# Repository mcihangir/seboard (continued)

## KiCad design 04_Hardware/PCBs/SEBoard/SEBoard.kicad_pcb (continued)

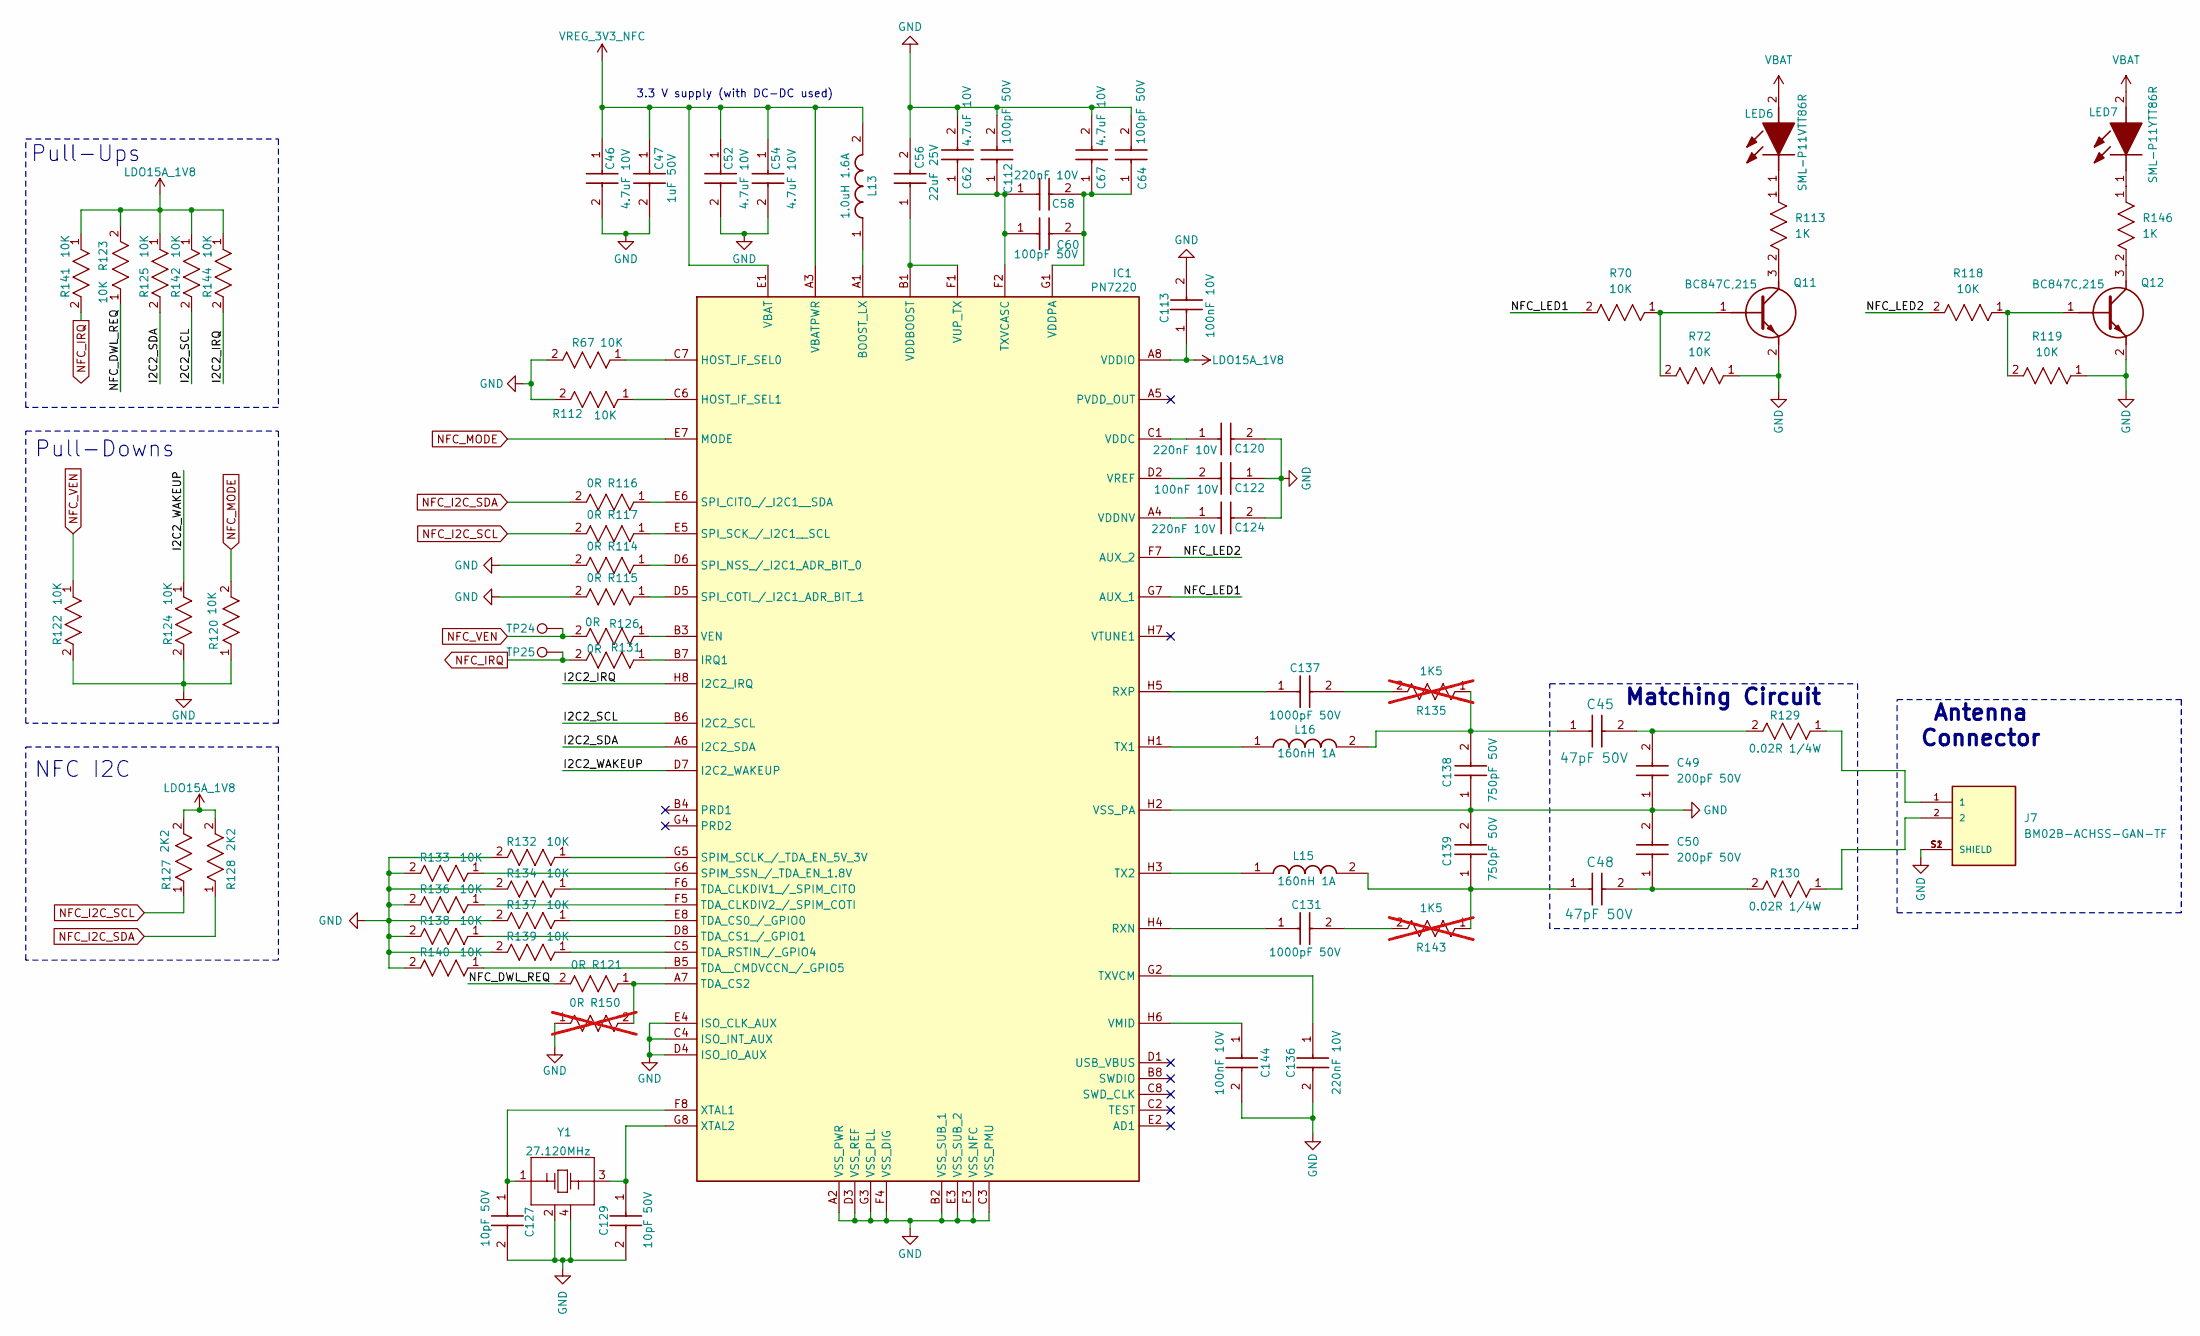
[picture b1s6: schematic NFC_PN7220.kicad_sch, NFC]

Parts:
C45, C48: 47pF 50V; CAP_CL10_SAM; Part Number 06035A470FAT2A
C46, C52, C54, C62, C67: 4.7uF 10V; CAPC1608X90N; Part Number LMK107BJ475KA-T
C47: 1uF 50V; CAPC1005X55N; Part Number GRM155R61H105KE05D
C49, C50: 200pF 50V; CAPC1608X87N; Part Number C0603C201F5GACTU
C56: 22uF 25V; CAPC2012X145N; Part Number GRM21BR61E226ME44L
C58, C120, C124, C136: 220nF 10V; CAPC1005X55N; Part Number GRM155R61A224JE19D
C60, C64, C112: 100pF 50V; CAPC1005X55N; Part Number GRM1555C1H101JA01J
C113, C122, C144: 100nF 10V; CAPC1005X55N; Part Number GRM155R71A104KA01D
C127, C129: 10pF 50V; CAPC1005X55N; Part Number GRM1555C1H100JA01D
C131, C137: 1000pF 50V; CAPC1608X80N; Part Number C1608C0G1H102F080AA
C138, C139: 750pF 50V; CAPC1608X87N; Part Number C0603C751F5GACTU
IC1: PN7220; BGA64C50P8X8_450X450X90; Part Number PN7220
J7: BM02B-ACHSS-GAN-TF; Part Number BM02B-ACHSS-GAN-TF(LF)(SN)
L13: 1.0uH 1.6A; LQM2HPN1R0MG0L; Part Number LQM2HPN1R0MG0L
L15, L16: 160nH 1A; LQW18CNR16J00D; Part Number LQW18CNR16J00D
LED6: SML-P11VTT86R; SMLP11VTT86R; Part Number SML-P11VTT86R
LED7: SML-P11YTT86R; SMLP11VTT86R; Part Number SML-P11YTT86R
Q11, Q12: BC847C,215; SOT95P230X110-3N; Part Number BC847C,215
R67, R70, R72, R112, R118, R119, R120, R122, R123, R124, R125, R132, R133, R134, R136, R137, R138, R139, R140, R141, R142, R144: 10K; RC0402N_YAG; Part Number RC0402JR-0710KL
R113, R146: 1K; RC0402N_YAG; Part Number RC0402JR-071KL
R114, R115, R116, R117, R121, R126, R131: 0R; RC0402N_YAG; Part Number RC0402JR-070RL
R127, R128: 2K2; RC0402N_YAG; Part Number RC0402JR-072K2L
R129, R130: 0.02R 1/4W; RESC2012X70N; Part Number RCWE080520L0FMEA
R135, R143: 1K5; ERJ3EKF1000V; Part Number ERJ-3GEYJ152V; not fitted
R150: 0R; RESC2012X50N; Part Number CRCW08050000Z0EA; not fitted
TP24, TP25: Sens_M; TestPoint_Pad_D1.0mm
Y1: 27.120MHz; ABM810000MHZ12D2W; Part Number ABM8-27.120MHZ-10-D1G-T

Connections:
/NFC_PN7220/I2C2_IRQ: IC1.H8 (I2C2_IRQ), R144.2
/NFC_PN7220/I2C2_SCL: IC1.B6 (I2C2_SCL), R142.2
/NFC_PN7220/I2C2_SDA: IC1.A6 (I2C2_SDA), R125.2
/NFC_PN7220/I2C2_WAKEUP: IC1.D7 (I2C2_WAKEUP), R124.1
/NFC_PN7220/NFC_DWL_REQ: R121.2, R123.1
/NFC_PN7220/NFC_LED1: IC1.G7 (AUX_1), R70.2
/NFC_PN7220/NFC_LED2: IC1.F7 (AUX_2), R118.2
GND: C46.2, C47.2, C49.1, C50.2, C52.2, C54.2, C56.2, C62.2, C64.2, C67.2, C112.2, C113.2, C120.2, C122.1, C124.2, C127.2, C129.2, C136.2, C138.1, C139.2, C144.2, IC1.A2 (VSS_PWR), IC1.B2 (VSS_SUB_1), IC1.C3 (VSS_PMU), IC1.C4 (ISO_INT_AUX), IC1.D3 (VSS_REF), IC1.D4 (ISO_IO_AUX), IC1.E3 (VSS_SUB_2), IC1.E4 (ISO_CLK_AUX), IC1.F3 (VSS_NFC), IC1.F4 (VSS_DIG), IC1.G3 (VSS_PLL), IC1.H2 (VSS_PA), J7.S1 (SHIELD), J7.S2 (SHIELD), Q11.2 (E), Q12.2 (E), R67.2, R72.1, R112.2, R114.2, R115.2, R119.1, R120.1, R122.2, R124.2, R132.2, R133.2, R134.2, R136.2, R137.2, R138.2, R139.2, R140.2, R150.1, Y1.2, Y1.4; also elsewhere on the board
LDO15A_1V8: C113.1, IC1.A8 (VDDIO), R123.2, R125.1, R127.2, R128.2, R141.1, R142.1, R144.1; also elsewhere on the board
NFC_I2C_SCL: R117.2, R127.1; also elsewhere on the board
NFC_I2C_SDA: R116.2, R128.1; also elsewhere on the board
NFC_IRQ: R131.2, R141.2, TP25.1 (1_1); also elsewhere on the board
NFC_MODE: IC1.E7 (MODE), R120.2; also elsewhere on the board
NFC_VEN: R122.1, R126.2, TP24.1 (1_1); also elsewhere on the board
unnamed: C45.2, C49.2, R129.2
unnamed: C48.2, C50.1, R130.2
unnamed: C131.2, R143.2
unnamed: C137.2, R135.2
unnamed: C45.1, C138.2, L16.2, R135.1
unnamed: C48.1, C139.1, L15.2, R143.1
unnamed: IC1.A1 (BOOST_LX), L13.1
unnamed: IC1.C7 (HOST_IF_SEL0), R67.1
unnamed: IC1.C6 (HOST_IF_SEL1), R112.1
unnamed: IC1.B7 (IRQ1), R131.1
unnamed: C131.1, IC1.H4 (RXN)
unnamed: C137.1, IC1.H5 (RXP)
unnamed: IC1.G5 (SPIM_SCLK_/_TDA_EN_5V_3V), R132.1
unnamed: IC1.G6 (SPIM_SSN_/_TDA_EN_1.8V), R133.1
unnamed: IC1.E6 (SPI_CITO_/_I2C1__SDA), R116.1
unnamed: IC1.D5 (SPI_COTI_/_I2C1_ADR_BIT_1), R115.1
unnamed: IC1.D6 (SPI_NSS_/_I2C1_ADR_BIT_0), R114.1
unnamed: IC1.E5 (SPI_SCK_/_I2C1__SCL), R117.1
unnamed: IC1.F6 (TDA_CLKDIV1_/_SPIM_CITO), R134.1
unnamed: IC1.F5 (TDA_CLKDIV2_/_SPIM_COTI), R136.1
unnamed: IC1.E8 (TDA_CS0_/_GPIO0), R137.1
unnamed: IC1.D8 (TDA_CS1_/_GPIO1), R138.1
unnamed: IC1.A7 (TDA_CS2), R121.1, R150.2
unnamed: IC1.C5 (TDA_RSTIN_/_GPIO4), R139.1
unnamed: IC1.B5 (TDA__CMDVCCN_/_GPIO5), R140.1
unnamed: IC1.H1 (TX1), L16.1
unnamed: IC1.H3 (TX2), L15.1
unnamed: C58.1, C60.1, C62.1, C112.1, IC1.F2 (TXVCASC)
unnamed: C136.1, IC1.G2 (TXVCM)
unnamed: C56.1, IC1.B1 (VDDBOOST), IC1.F1 (VUP_TX)
unnamed: C120.1, IC1.C1 (VDDC)
unnamed: C124.1, IC1.A4 (VDDNV)
unnamed: C58.2, C60.2, C64.1, C67.1, IC1.G1 (VDDPA)
unnamed: IC1.B3 (VEN), R126.1
unnamed: C144.1, IC1.H6 (VMID)
unnamed: C122.2, IC1.D2 (VREF)
unnamed: C127.1, IC1.F8 (XTAL1), Y1.1
unnamed: C129.1, IC1.G8 (XTAL2), Y1.3
unnamed: J7.1, R129.1
unnamed: J7.2, R130.1
unnamed: LED6.1 (K), R113.1
unnamed: LED7.1 (K), R146.1
unnamed: Q11.1 (B), R70.1, R72.2
unnamed: Q11.3 (C), R113.2
unnamed: Q12.1 (B), R118.1, R119.2
unnamed: Q12.3 (C), R146.2
VBAT: LED6.2 (A), LED7.2 (A); also elsewhere on the board
VREG_3V3_NFC: C46.1, C47.1, C52.1, C54.1, IC1.A3 (VBATPWR), IC1.E1 (VBAT), L13.2; also elsewhere on the board

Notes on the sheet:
NFC I2C
Pull-Ups
Antenna Connector
3.3 V supply (with DC-DC used)
Matching Circuit
Pull-Downs

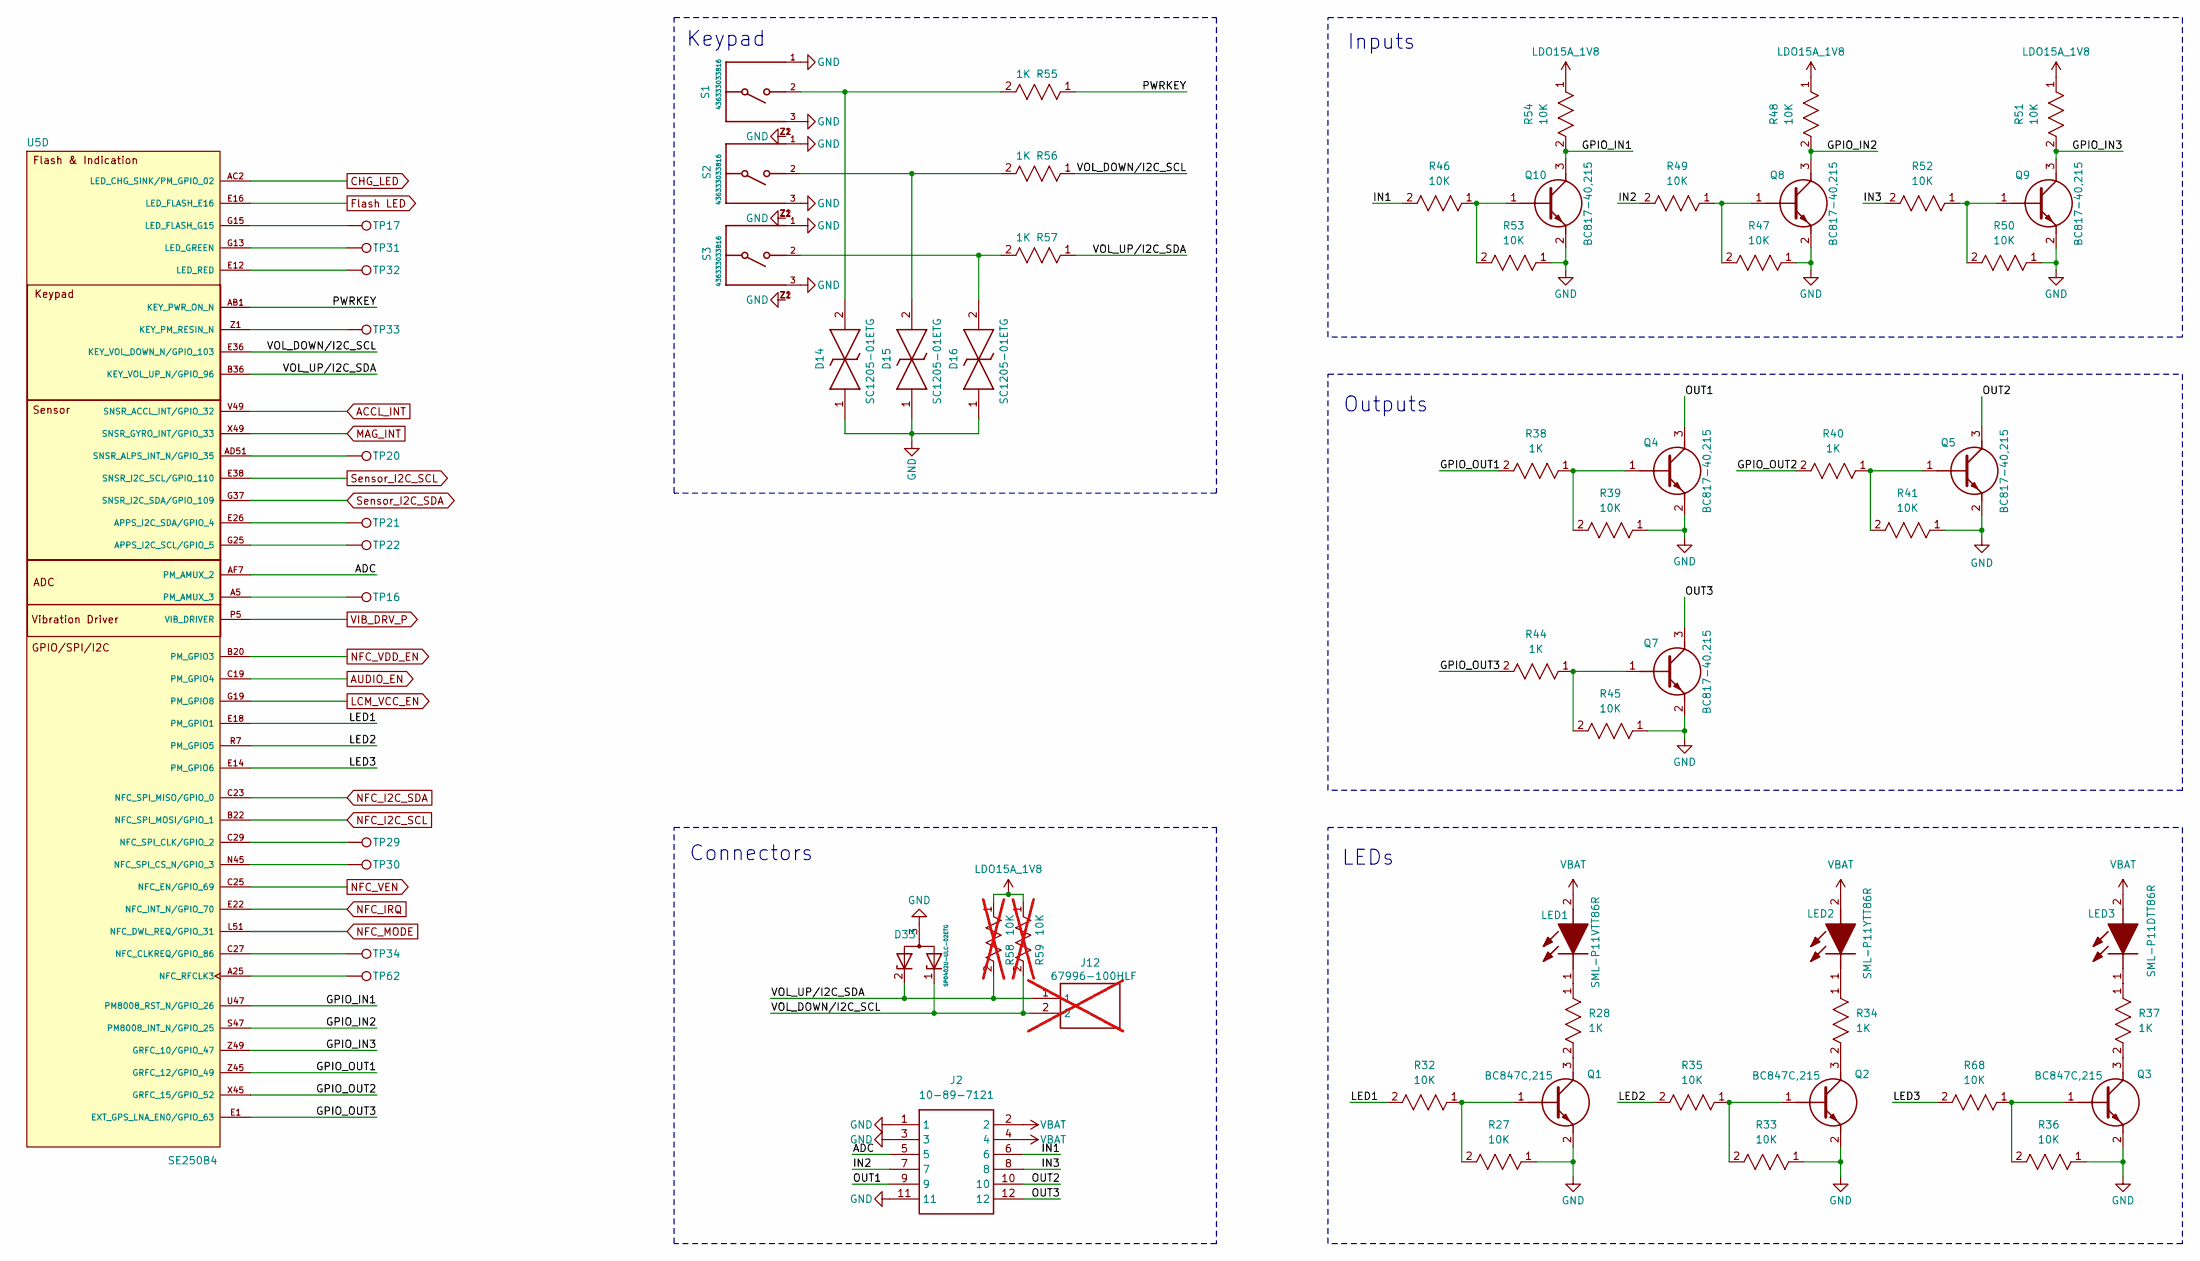
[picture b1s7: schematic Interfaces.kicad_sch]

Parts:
D14, D15, D16: SC1205-01ETG; SC120501ETG; Part Number SC1205-01ETG
D33: SP0402U-ULC-02ETG; SESD0402Q2UG0020090; Part Number SP0402U-ULC-02ETG
J2: 10-89-7121; HDRV12W87P254X254_2X6; Part Number 10-89-7121
J12: 67996-100HLF; HDRV2W67P254_2X1_254X483X858P; Part Number 67996-100HLF; not fitted
LED1: SML-P11VTT86R; SMLP11VTT86R; Part Number SML-P11VTT86R
LED2: SML-P11YTT86R; SMLP11VTT86R; Part Number SML-P11YTT86R
LED3: SML-P11DTT86R; SMLP11VTT86R; Part Number SML-P11DTT86R
Q1, Q2, Q3: BC847C,215; SOT95P230X110-3N; Part Number BC847C,215
Q4, Q5, Q7, Q8, Q9, Q10: BC817-40,215; BC81740215; Part Number BC817-40,215
R27, R32, R33, R35, R36, R39, R41, R45, R46, R47, R48, R49, R50, R51, R52, R53, R54, R68: 10K; RC0402N_YAG; Part Number RC0402JR-0710KL
R28, R34, R37, R38, R40, R44, R55, R56, R57: 1K; RC0402N_YAG; Part Number RC0402JR-071KL
R58, R59: 10K; RC0402N_YAG; Part Number RC0402JR-0710KL; not fitted
S1, S2, S3: 436333033816; Part Number 436333033816
TP16, TP17, TP20, TP21, TP22, TP29, TP30, TP31, TP32, TP33, TP34, TP62: Sens_M; TestPoint_Pad_D1.0mm
U5: SE250B4; XCVR_SE250B4-NA; Part Number SE250B4-EU

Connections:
/Interfaces/ADC: J2.5, U5.AF7 (PM_AMUX_2)
/Interfaces/GPIO_IN1: Q10.3 (C), R54.2, U5.U47 (PM8008_RST_N/GPIO_26)
/Interfaces/GPIO_IN2: Q8.3 (C), R48.2, U5.S47 (PM8008_INT_N/GPIO_25)
/Interfaces/GPIO_IN3: Q9.3 (C), R51.2, U5.Z49 (GRFC_10/GPIO_47)
/Interfaces/GPIO_OUT1: R38.2, U5.Z45 (GRFC_12/GPIO_49)
/Interfaces/GPIO_OUT2: R40.2, U5.X45 (GRFC_15/GPIO_52)
/Interfaces/GPIO_OUT3: R44.2, U5.E1 (EXT_GPS_LNA_EN0/GPIO_63)
/Interfaces/IN1: J2.6, R46.2
/Interfaces/IN2: J2.7, R49.2
/Interfaces/IN3: J2.8, R52.2
/Interfaces/LED1: R32.2, U5.E18 (PM_GPIO1)
/Interfaces/LED2: R35.2, U5.R7 (PM_GPIO5)
/Interfaces/LED3: R68.2, U5.E14 (PM_GPIO6)
/Interfaces/OUT1: J2.9, Q4.3 (C)
/Interfaces/OUT2: J2.10, Q5.3 (C)
/Interfaces/OUT3: J2.12, Q7.3 (C)
/Interfaces/PWRKEY: R55.1, U5.AB1 (KEY_PWR_ON_N)
/Interfaces/VOL_DOWN/I2C_SCL: D33.1 (K_1), J12.2, R56.1, R59.2, U5.E36 (KEY_VOL_DOWN_N/GPIO_103)
/Interfaces/VOL_UP/I2C_SDA: D33.2 (K_2), J12.1, R57.1, R58.2, U5.B36 (KEY_VOL_UP_N/GPIO_96)
ACCL_INT: U5.V49 (SNSR_ACCL_INT/GPIO_32); also elsewhere on the board
AUDIO_EN: U5.C19 (PM_GPIO4); also elsewhere on the board
CHG_LED: U5.AC2 (LED_CHG_SINK/PM_GPIO_02); also elsewhere on the board
Flash LED: U5.E16 (LED_FLASH_E16); also elsewhere on the board
GND: D14.1, D15.1, D16.1, D33.3 (GND), J2.1, J2.3, J2.11, Q1.2 (E), Q2.2 (E), Q3.2 (E), Q4.2 (E), Q5.2 (E), Q7.2 (E), Q8.2 (E), Q9.2 (E), Q10.2 (E), R27.1, R33.1, R36.1, R39.1, R41.1, R45.1, R47.1, R50.1, R53.1, S1.1, S1.3, S1.Z1, S1.Z2, S2.1, S2.3, S2.Z1, S2.Z2, S3.1, S3.3, S3.Z1, S3.Z2; also elsewhere on the board
LCM_VCC_EN: U5.G19 (PM_GPIO8); also elsewhere on the board
LDO15A_1V8: R48.1, R51.1, R54.1, R58.1, R59.1; also elsewhere on the board
MAG_INT: U5.X49 (SNSR_GYRO_INT/GPIO_33); also elsewhere on the board
NFC_I2C_SCL: U5.B22 (NFC_SPI_MOSI/GPIO_1); also elsewhere on the board
NFC_I2C_SDA: U5.C23 (NFC_SPI_MISO/GPIO_0); also elsewhere on the board
NFC_IRQ: U5.E22 (NFC_INT_N/GPIO_70); also elsewhere on the board
NFC_MODE: U5.L51 (NFC_DWL_REQ/GPIO_31); also elsewhere on the board
NFC_VDD_EN: U5.B20 (PM_GPIO3); also elsewhere on the board
NFC_VEN: U5.C25 (NFC_EN/GPIO_69); also elsewhere on the board
unnamed: D14.2, R55.2, S1.2
unnamed: D15.2, R56.2, S2.2
unnamed: D16.2, R57.2, S3.2
unnamed: LED1.1 (K), R28.1
unnamed: LED2.1 (K), R34.1
unnamed: LED3.1 (K), R37.1
unnamed: Q1.1 (B), R27.2, R32.1
unnamed: Q1.3 (C), R28.2
unnamed: Q2.1 (B), R33.2, R35.1
unnamed: Q2.3 (C), R34.2
unnamed: Q3.1 (B), R36.2, R68.1
unnamed: Q3.3 (C), R37.2
unnamed: Q4.1 (B), R38.1, R39.2
unnamed: Q5.1 (B), R40.1, R41.2
unnamed: Q7.1 (B), R44.1, R45.2
unnamed: Q8.1 (B), R47.2, R49.1
unnamed: Q9.1 (B), R50.2, R52.1
unnamed: Q10.1 (B), R46.1, R53.2
unnamed: TP22.1 (1_1), U5.G25 (APPS_I2C_SCL/GPIO_5)
unnamed: TP21.1 (1_1), U5.E26 (APPS_I2C_SDA/GPIO_4)
unnamed: TP33.1 (1_1), U5.Z1 (KEY_PM_RESIN_N)
unnamed: TP17.1 (1_1), U5.G15 (LED_FLASH_G15)
unnamed: TP31.1 (1_1), U5.G13 (LED_GREEN)
unnamed: TP32.1 (1_1), U5.E12 (LED_RED)
unnamed: TP34.1 (1_1), U5.C27 (NFC_CLKREQ/GPIO_86)
unnamed: TP62.1 (1_1), U5.A25 (NFC_RFCLK3)
unnamed: TP29.1 (1_1), U5.C29 (NFC_SPI_CLK/GPIO_2)
unnamed: TP30.1 (1_1), U5.N45 (NFC_SPI_CS_N/GPIO_3)
unnamed: TP16.1 (1_1), U5.A5 (PM_AMUX_3)
unnamed: TP20.1 (1_1), U5.AD51 (SNSR_ALPS_INT_N/GPIO_35)
Sensor_I2C_SCL: U5.E38 (SNSR_I2C_SCL/GPIO_110); also elsewhere on the board
Sensor_I2C_SDA: U5.G37 (SNSR_I2C_SDA/GPIO_109); also elsewhere on the board
VBAT: J2.2, J2.4, LED1.2 (A), LED2.2 (A), LED3.2 (A); also elsewhere on the board
VIB_DRV_P: U5.P5 (VIB_DRIVER); also elsewhere on the board

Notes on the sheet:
Inputs
LEDs
Outputs
Keypad
Connectors

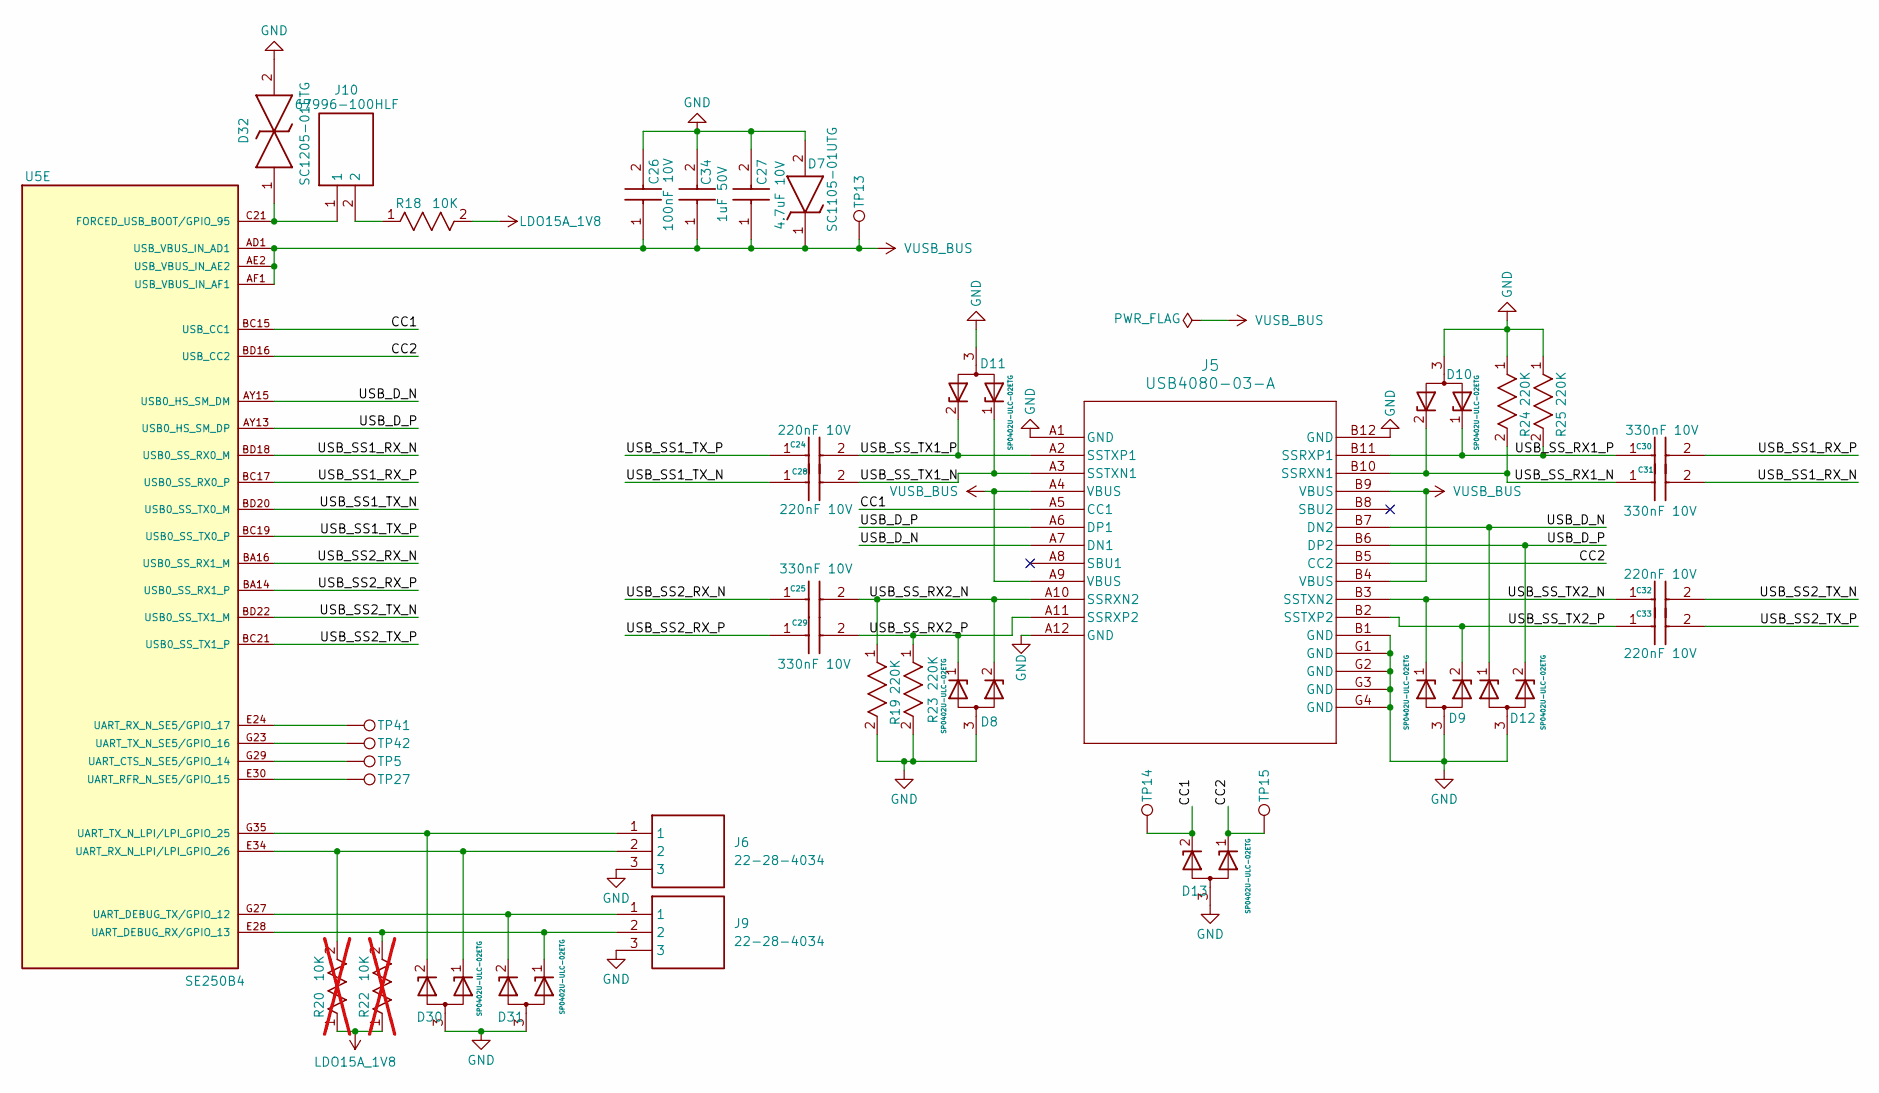
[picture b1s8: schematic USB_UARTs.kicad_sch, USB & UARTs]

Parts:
C24, C28, C32, C33: 220nF 10V; CAPC1005X55N; Part Number GRM155R61A224JE19D
C25, C29, C30, C31: 330nF 10V; CAPC1005X55N; Part Number GRM155R61A334KE15D
C26: 100nF 10V; CAPC1005X55N; Part Number GRM155R71A104KA01D
C27: 4.7uF 10V; CAPC1608X90N; Part Number LMK107BJ475KA-T
C34: 1uF 50V; CAPC1005X55N; Part Number GRM155R61H105KE05D
D7: SC1105-01UTG; SC110501UTG; Part Number SC1105-01UTG
D8, D9, D10, D11, D12, D13, D30, D31: SP0402U-ULC-02ETG; SESD0402Q2UG0020090; Part Number SP0402U-ULC-02ETG
D32: SC1205-01ETG; SC120501ETG; Part Number SC1205-01ETG
J5: USB4080-03-A; GCT_USB4080-03-A_REVA; Part Number USB4080-03-A
J6, J9: 22-28-4034; HDRV3W66P0X254_1X3_762X249X1042P; Part Number 22-28-4034
J10: 67996-100HLF; HDRV2W67P254_2X1_254X483X858P; Part Number 67996-100HLF
R18: 10K; RC0402N_YAG; Part Number RC0402JR-0710KL
R19, R23, R24, R25: 220K; RC0402N_YAG; Part Number RC0402FR-07220KL
R20, R22: 10K; RC0402N_YAG; Part Number RC0402JR-0710KL; not fitted
TP5, TP13, TP14, TP15, TP27, TP41, TP42: Sens_M; TestPoint_Pad_D1.0mm
U5: SE250B4; XCVR_SE250B4-NA; Part Number SE250B4-EU

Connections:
/USB_UARTs/CC1: D13.2 (K_2), J5.A5 (CC1), TP14.1 (1_1), U5.BC15 (USB_CC1)
/USB_UARTs/CC2: D13.1 (K_1), J5.B5 (CC2), TP15.1 (1_1), U5.BD16 (USB_CC2)
/USB_UARTs/USB_D_N: D12.1 (K_1), J5.A7 (DN1), J5.B7 (DN2), U5.AY15 (USB0_HS_SM_DM)
/USB_UARTs/USB_D_P: D12.2 (K_2), J5.A6 (DP1), J5.B6 (DP2), U5.AY13 (USB0_HS_SM_DP)
/USB_UARTs/USB_SS1_RX_N: C31.2, U5.BD18 (USB0_SS_RX0_M)
/USB_UARTs/USB_SS1_RX_P: C30.2, U5.BC17 (USB0_SS_RX0_P)
/USB_UARTs/USB_SS1_TX_N: C28.1, U5.BD20 (USB0_SS_TX0_M)
/USB_UARTs/USB_SS1_TX_P: C24.1, U5.BC19 (USB0_SS_TX0_P)
/USB_UARTs/USB_SS2_RX_N: C25.1, U5.BA16 (USB0_SS_RX1_M)
/USB_UARTs/USB_SS2_RX_P: C29.1, U5.BA14 (USB0_SS_RX1_P)
/USB_UARTs/USB_SS2_TX_N: C32.2, U5.BD22 (USB0_SS_TX1_M)
/USB_UARTs/USB_SS2_TX_P: C33.2, U5.BC21 (USB0_SS_TX1_P)
/USB_UARTs/USB_SS_RX1_N: C31.1, D10.2 (K_2), J5.B10 (SSRXN1), R24.2
/USB_UARTs/USB_SS_RX1_P: C30.1, D10.1 (K_1), J5.B11 (SSRXP1), R25.2
/USB_UARTs/USB_SS_RX2_N: C25.2, D8.2 (K_2), J5.A10 (SSRXN2), R19.1
/USB_UARTs/USB_SS_RX2_P: C29.2, D8.1 (K_1), J5.A11 (SSRXP2), R23.1
/USB_UARTs/USB_SS_TX1_N: C28.2, D11.1 (K_1), J5.A3 (SSTXN1)
/USB_UARTs/USB_SS_TX1_P: C24.2, D11.2 (K_2), J5.A2 (SSTXP1)
/USB_UARTs/USB_SS_TX2_N: C32.1, D9.1 (K_1), J5.B3 (SSTXN2)
/USB_UARTs/USB_SS_TX2_P: C33.1, D9.2 (K_2), J5.B2 (SSTXP2)
GND: C26.2, C27.2, C34.2, D7.2 (A), D8.3 (GND), D9.3 (GND), D10.3 (GND), D11.3 (GND), D12.3 (GND), D13.3 (GND), D30.3 (GND), D31.3 (GND), D32.2, J5.A1 (GND), J5.A12 (GND), J5.B1 (GND), J5.B12 (GND), J5.G1 (GND), J5.G2 (GND), J5.G3 (GND), J5.G4 (GND), J6.3, J9.3, R19.2, R23.2, R24.1, R25.1; also elsewhere on the board
LDO15A_1V8: R18.2, R20.1, R22.1; also elsewhere on the board
unnamed: D30.1 (K_1), J6.2, R20.2, U5.E34 (UART_RX_N_LPI/LPI_GPIO_26)
unnamed: D30.2 (K_2), J6.1, U5.G35 (UART_TX_N_LPI/LPI_GPIO_25)
unnamed: D31.1 (K_1), J9.2, R22.2, U5.E28 (UART_DEBUG_RX/GPIO_13)
unnamed: D31.2 (K_2), J9.1, U5.G27 (UART_DEBUG_TX/GPIO_12)
unnamed: J10.2, R18.1
unnamed: D32.1, J10.1, U5.C21 (FORCED_USB_BOOT/GPIO_95)
unnamed: TP5.1 (1_1), U5.G29 (UART_CTS_N_SE5/GPIO_14)
unnamed: TP27.1 (1_1), U5.E30 (UART_RFR_N_SE5/GPIO_15)
unnamed: TP41.1 (1_1), U5.E24 (UART_RX_N_SE5/GPIO_17)
unnamed: TP42.1 (1_1), U5.G23 (UART_TX_N_SE5/GPIO_16)
VUSB_BUS: C26.1, C27.1, C34.1, D7.1 (K), J5.A4 (VBUS), J5.A9 (VBUS), J5.B4 (VBUS), J5.B9 (VBUS), TP13.1 (1_1), U5.AD1 (USB_VBUS_IN_AD1), U5.AE2 (USB_VBUS_IN_AE2), U5.AF1 (USB_VBUS_IN_AF1)

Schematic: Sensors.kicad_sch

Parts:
B1: HD-EMB1104-SM-2; PUI_HD-EMB1104-SM-2; Part Number HD-EMB1104-SM-2
C39, C114: 100nF 10V; CAPC1005X55N; Part Number GRM155R71A104KA01D
C40, C41: 1uF 50V; CAPC1005X55N; Part Number GRM155R61H105KE05D
C42: 4.7uF 10V; CAPC1608X90N; Part Number LMK107BJ475KA-T
C115: 10uF 6.3V; CAPC1005X55N; Part Number GRM155R60J106ME15D
D17: B140WS-7; SOD2513X120N; Part Number B140WS-7
LED4: SML-P11VTT86R; SMLP11VTT86R; Part Number SML-P11VTT86R
R60: 33R; RC0402N_YAG; Part Number RC0402JR-0733RL
R61, R62, R65: 2K2; RC0402N_YAG; Part Number RC0402JR-072K2L
R63, R64: 0R; RC0402N_YAG; Part Number RC0402JR-070RL
TP23: Sens_M; TestPoint_Pad_D1.0mm
U6: LIS2DH12TR; LGA-12_STM; Part Number LIS2DH12TR
U7: MMC3630KJ; BGA8C40P3X3_120X120X57; Part Number MMC3630KJ

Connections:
ACCL_INT: U6.12 (INT1); also elsewhere on the board
CHG_LED: R65.2; also elsewhere on the board
GND: B1.SH1 (SHIELD_SH1), C39.2, C40.2, C41.2, C42.1, C114.2, C115.2, D17.2 (A), R63.2, U6.3 (SDO/SA0), U6.5 (RES), U6.6 (GND), U6.7 (GND), U6.8 (GND), U7.B1 (VSA); also elsewhere on the board
LDO15A_1V8: C41.1, C114.1, R60.2, R61.2, R62.2, U6.10 (VDD_IO), U7.C1 (VDD); also elsewhere on the board
LDO17A_3V0: C39.1, C42.2, C115.1, U6.9 (VDD), U7.A1 (VCAP); also elsewhere on the board
MAG_INT: U7.C2 (INT); also elsewhere on the board
unnamed: B1.N, R63.1
unnamed: B1.P, C40.1, D17.1 (K), R64.1
unnamed: LED4.1 (K), R65.1
unnamed: R60.1, U6.2 (CS)
unnamed: TP23.1 (1_1), U6.11 (INT2)
Sensor_I2C_SCL: R62.1, U6.1 (SCL/SPC), U7.B3 (SLC); also elsewhere on the board
Sensor_I2C_SDA: R61.1, U6.4 (SDA/SDI/SDO), U7.C3 (SDA); also elsewhere on the board
VBAT: LED4.2 (A); also elsewhere on the board
VIB_DRV_P: R64.2; also elsewhere on the board

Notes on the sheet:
Charging LED
Accelerometer MEMS
Hall Effect/Magnetic
Vibrator Motor
Sensor I2C

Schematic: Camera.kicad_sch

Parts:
C68, C71: 4.7uF 6.3V; CAPC1005X55N; Part Number GRM155R60J475ME47D
C69, C72, C116, C117: 100nF 10V; CAPC1005X55N; Part Number GRM155R71A104KA01D
C70, C118: 1uF 50V; CAPC1005X55N; Part Number GRM155R61H105KE05D
FL1, FL2, FL3, FL4, FL5: LCFE121002A900TG; Part Number LCFE121002A900TG
J13: YXT-BB10-30S-02; YXT_YXT-BB10-30S-02; Part Number YXT-BB10-30S-02
L5, L7, L8: 600ohm 100MHz; 0402; Part Number 7427927291
L6: 70ohm 100MHz; 0402; Part Number 7427927370
LED5: LTPL-C0676WPGB; Part Number LTPL-C0676WPGB
R73, R74: 0R; RC0402N_YAG; Part Number RC0402JR-070RL
R75: 10K; RC0402N_YAG; Part Number RC0402JR-0710KL
R76, R77: 2K2; RC0402N_YAG; Part Number RC0402JR-072K2L
TP38, TP39, TP43, TP44, TP45, TP46, TP47, TP48, TP53: VBAT; TestPoint_Pad_D1.0mm
U5: SE250B4; XCVR_SE250B4-NA; Part Number SE250B4-EU

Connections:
/Camera/CAM0_I2C_SCL: J13.22 (SCL), R76.1, U5.AG47 (CAM_CCI_I2C_SCL0/GPIO_23)
/Camera/CAM0_I2C_SDA: J13.21 (SDA), R77.1, U5.AE47 (CAM_CCI_I2C_SDA0/GPIO_22)
/Camera/CAM0_PWDN: R73.2, U5.L49 (CAM0_PWDN/GPIO_97)
/Camera/CLK_N: FL1.4, J13.3 (MCN)
/Camera/CLK_P: FL1.3, J13.2 (MCP)
/Camera/CSI0_CLK_N: FL1.1, U5.AU49 (MIPI_CSI0_A0_CLK_M)
/Camera/CSI0_CLK_P: FL1.2, U5.AT50 (MIPI_CSI0_NC_CLK_P)
/Camera/CSI0_LN0_N: FL2.1, U5.AS49 (MIPI_CSI0_C0_LN0_M)
/Camera/CSI0_LN0_P: FL2.2, U5.AR50 (MIPI_CSI0_B0_LN0_P)
/Camera/CSI0_LN1_N: FL3.1, U5.AT47 (MIPI_CSI0_B1_LN1_M)
/Camera/CSI0_LN1_P: FL3.2, U5.AS45 (MIPI_CSI0_A1_LN1_P)
/Camera/CSI0_LN2_N: FL4.2, U5.AP45 (MIPI_CSI0_A2_LN2_M)
/Camera/CSI0_LN2_P: FL4.1, U5.AN47 (MIPI_CSI0_C1_LN2_P)
/Camera/CSI0_LN3_N: FL5.2, U5.AP49 (MIPI_CSI0_C2_LN3_M)
/Camera/CSI0_LN3_P: FL5.1, U5.AR47 (MIPI_CSI0_B2_LN3_P)
/Camera/MD0_N: FL2.4, J13.9 (MDN0)
/Camera/MD0_P: FL2.3, J13.8 (MDP0)
/Camera/MD1_N: FL3.4, J13.15 (MDN1)
/Camera/MD1_P: FL3.3, J13.14 (MDP1)
/Camera/MD2_N: FL4.3, J13.6 (MDN2)
/Camera/MD2_P: FL4.4, J13.5 (MDP2)
/Camera/MD3_N: FL5.3, J13.12 (MDN3)
/Camera/MD3_P: FL5.4, J13.11 (MDP3)
CAM0_1V1_EN: U5.K47 (CAM_1P2_EN/GPIO_58); also elsewhere on the board
Flash LED: LED5.1 (+), LED5.2 (+); also elsewhere on the board
GND: C68.2, C69.2, C70.2, C71.2, C72.2, C116.2, C117.2, C118.2, FL1.5, FL1.6, FL2.5, FL2.6, FL3.5, FL3.6, FL4.5, FL4.6, FL5.5, FL5.6, J13.1 (AGND), J13.4 (DGND), J13.7 (DGND), J13.10 (DGND), J13.13 (DGND), J13.16 (DGND), J13.18 (DGND), J13.24 (DGND), J13.26 (DGND), J13.28 (GND), J13.31 (SHIELD), J13.32 (SHIELD), J13.33 (SHIELD), J13.34 (SHIELD), LED5.3 (-); also elsewhere on the board
LDO15A_1V8: L8.2, R75.1, R76.2, R77.2; also elsewhere on the board
unnamed: C68.1, C116.1, J13.30 (AF_VDD_2V8), L5.1
unnamed: C69.1, C71.1, J13.29 (AVDD_2V95), L7.1
unnamed: C117.1, C118.1, J13.27 (DOVDD1V8), L8.1
unnamed: C70.1, C72.1, J13.23 (DVDD_1V2), L6.1
unnamed: J13.17 (ID(DOVDD)), R75.2
unnamed: J13.25 (MCLK), U5.AJ50 (CAM_MCLK0/GPIO_20)
unnamed: J13.20 (NC(RESET)), R74.1
unnamed: J13.19 (PWDN), R73.1
unnamed: R74.2, U5.AF51 (CAM0_RST_N/GPIO_18)
unnamed: TP44.1 (1_1), U5.AD45 (CAM1_PWDN/GPIO_36)
unnamed: TP43.1 (1_1), U5.Y47 (CAM1_RST_N/GPIO_19)
unnamed: TP47.1 (1_1), U5.V45 (CAM2_RST_N/GPIO_24)
unnamed: TP38.1 (1_1), U5.H50 (CAM_1P8_EN/GPIO_39)
unnamed: TP39.1 (1_1), U5.E51 (CAM_2P8_EN/GPIO_42)
unnamed: TP53.1 (1_1), U5.J49 (CAM_AF_VDD_EN/GPIO_38)
unnamed: TP45.1 (1_1), U5.AG50 (CAM_MCLK1/GPIO_21)
unnamed: TP46.1 (1_1), U5.AL50 (CAM_MCLK2/GPIO_27)
unnamed: TP48.1 (1_1), U5.C37 (TS_3P0_EN/GPIO_104)
VDD_2V8: L5.2, L7.2; also elsewhere on the board
VREG_1V1: L6.2; also elsewhere on the board

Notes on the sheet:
Main Camera

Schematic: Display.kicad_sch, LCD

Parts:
C73, C74, C78: 1uF 50V; CAPC1005X55N; Part Number GRM155R61H105KE05D
C75: 1nF 50V; CAPC1005X55N; Part Number GRM1555C1H102JA01D
C76, C79: 4.7uF 6.3V; CAPC1005X55N; Part Number GRM155R60J475ME47D
C77, C80: 100nF 10V; CAPC1005X55N; Part Number GRM155R71A104KA01D
D18: B140WS-7; SOD2513X120N; Part Number B140WS-7
D19: SRV05-4.TCT; SOT95P280X145-6N; Part Number SRV05-4.TCT
FL6, FL7, FL8, FL9, FL10: LCFE121002A900TG; Part Number LCFE121002A900TG
IC3: PCA9306DCTT; SOP65P400X130-8N; Part Number PCA9306DCTT
IC4: TXS0102DCUR; SOP50P310X90-8N; Part Number TXS0102DCUR
J14: FH12S-30S-0.5SH_55_; FH12S30S05SH55; Part Number FH12S-30S-0.5SH(55)
J15: FH12-8S-0.5SH_55_; FH128S05SH55; Part Number FH12-8S-0.5SH(55)
L9: 22uH 1.364ohm 0.46A; VLS2520; Part Number VLS252010CX-220M-1
L10, L11, L12: 600ohm 100MHz; 0402; Part Number 7427927291
R14: 0R; RESC2012X50N; Mouser Part Number 71-CRCW0805-0-E3
R15: 0R; RESC2012X50N; Mouser Part Number 71-CRCW0805-0-E3; not fitted
R26: 200K; RC0402N_YAG; Part Number RC0402FR-07200KL
R78: 10K; RC0402N_YAG; Part Number RC0402JR-0710KL
R79: 2R4; RC0402N_YAG; Part Number RC0402JR-072R4L
R81: 4K7; RC0402N_YAG; Part Number RC0402JR-074K7L; not fitted
R148, R149, R151, R152: 2K2; RC0402N_YAG; Part Number RC0402JR-072K2L
TP28, TP35, TP36, TP37, TP40: Sens_M; TestPoint_Pad_D1.0mm
U5: SE250B4; XCVR_SE250B4-NA; Part Number SE250B4-EU
U9: AP5724WG-7; SOT95P285X140-6N; Part Number AP5724WG-7

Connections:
/Display/CLK_N: FL6.4, J14.13
/Display/CLK_P: FL6.3, J14.14
/Display/CTP_INT: D19.4 (I/O3), IC4.1 (B2), J15.6
/Display/CTP_RST: D19.6 (I/O4), IC4.8 (B1), J15.7
/Display/CTP_SCL: D19.3 (I/O2), IC3.6 (SCL2), J15.4, R152.2
/Display/CTP_SDA: D19.1 (I/O1), IC3.5 (SDA2), J15.5, R151.2
/Display/CTP_VDD: C79.2, C80.2, D19.5 (VBUS), J15.3, L12.2
/Display/D0_N: FL10.4, J14.7
/Display/D0_P: FL10.3, J14.8
/Display/D1_N: FL9.4, J14.10
/Display/D1_P: FL9.3, J14.11
/Display/D2_N: FL8.4, J14.16
/Display/D2_P: FL8.3, J14.17
/Display/D3_N: FL7.4, J14.19
/Display/D3_P: FL7.3, J14.20
/Display/DSI_CLK_N: FL6.1, U5.BC27 (MIPI_DSI0_CLK_M)
/Display/DSI_CLK_P: FL6.2, U5.BC25 (MIPI_DSI0_CLK_P)
/Display/DSI_LN0_N: FL10.1, U5.BA24 (MIPI_DSI0_L0_M)
/Display/DSI_LN0_P: FL10.2, U5.BA22 (MIPI_DSI0_L0_P)
/Display/DSI_LN1_N: FL9.1, U5.AY25 (MIPI_DSI0_L1_M)
/Display/DSI_LN1_P: FL9.2, U5.AY27 (MIPI_DSI0_L1_P)
/Display/DSI_LN2_N: FL8.1, U5.AY23 (MIPI_DSI0_L2_M)
/Display/DSI_LN2_P: FL8.2, U5.AY21 (MIPI_DSI0_L2_P)
/Display/DSI_LN3_N: FL7.1, U5.BD26 (MIPI_DSI0_L3_M)
/Display/DSI_LN3_P: FL7.2, U5.BD28 (MIPI_DSI0_L3_P)
/Display/IOVCC: C78.2, J14.27, L11.2
/Display/LED1-: J14.2, R79.1, U9.3 (FB)
/Display/LED+: C74.1, C75.1, D18.1 (K), J14.4, U9.5 (OVP)
/Display/PWM: R78.1, U5.E20 (LCM_WLED_PWM), U9.4 (EN)
/Display/RESET: J14.26, U5.B30 (LCM_RST_N)
/Display/TE: J14.25, U5.B38 (LCM_TE/GPIO_81)
/Display/TP_INT: IC4.4 (A2), R81.2, U5.C31 (TS_INT_N/GPIO_80)
/Display/TP_RST: IC4.5 (A1), U5.C35 (TS_RESET_N/GPIO_71)
/Display/TP_SCL: IC3.3 (SCL1), R149.2, U5.E32 (TS_I2C_SCL/GPIO_7)
/Display/TP_SDA: IC3.4 (SDA1), R148.2, U5.G31 (TS_I2C_SDA/GPIO_6)
/Display/VCI: C76.2, C77.2, J14.28, L10.2
GND: C73.2, C74.2, C75.2, C76.1, C77.1, C78.1, C79.1, C80.1, D19.2 (GND), FL6.5, FL6.6, FL7.5, FL7.6, FL8.5, FL8.6, FL9.5, FL9.6, FL10.5, FL10.6, IC3.1 (GND), IC4.2 (GND), J14.6, J14.9, J14.12, J14.15, J14.18, J14.21, J14.22, J14.24, J14.29, J14.30, J14.MP1, J14.MP2, J15.1, J15.8, J15.MP1, J15.MP2, R78.2, R79.2, U9.2 (GND); also elsewhere on the board
LCM_VCC: IC4.7 (VCCB), L10.1, L12.1, R14.2, R15.2, R26.1, R151.1, R152.1
LDO15A_1V8: IC3.2 (VREF1), IC4.3 (VCCA), IC4.6 (OE), L11.1, R81.1, R148.1, R149.1; also elsewhere on the board
LDO17A_3V0: R15.1; also elsewhere on the board
unnamed: D18.2 (A), L9.2, U9.1 (SW)
unnamed: IC3.7 (VREF2), IC3.8 (EN), R26.2
unnamed: TP40.1 (1_1), U5.T49 (HDMI_INT/GPIO_34)
unnamed: TP35.1 (1_1), U5.AW3 (LCM_1P8_EN/GPIO_114)
unnamed: TP37.1 (1_1), U5.W47 (LCM_2P8_EN/GPIO_60)
unnamed: TP36.1 (1_1), U5.AY3 (LCM_BL_EN/GPIO_113)
unnamed: TP28.1 (1_1), U5.G51 (TS_3P0_EN/GPIO_37)
VPH_PWR: C73.1, L9.1, U9.6 (VIN); also elsewhere on the board
VREG_3V3: R14.1; also elsewhere on the board

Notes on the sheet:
LCD BACKLIGHT
LCD
TOUCH PANEL
Pull Ups
LCM Power Supply Selection
